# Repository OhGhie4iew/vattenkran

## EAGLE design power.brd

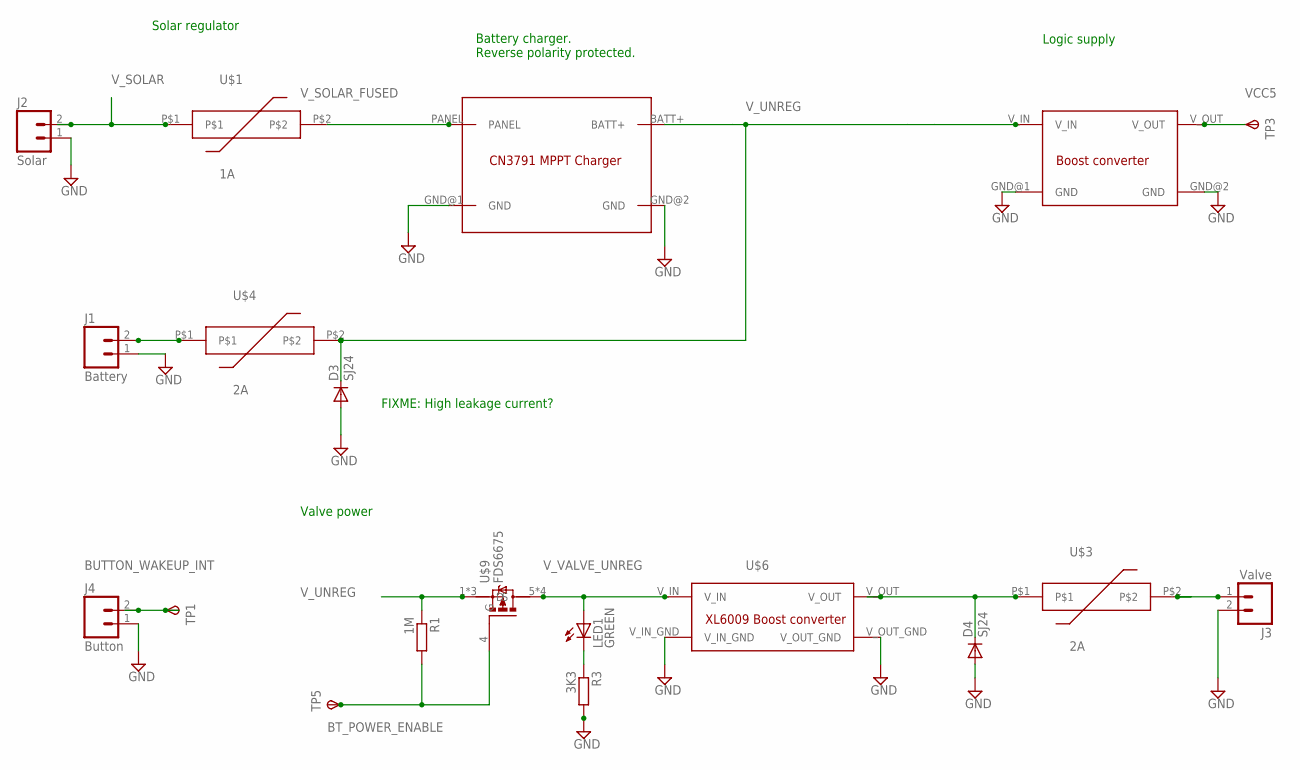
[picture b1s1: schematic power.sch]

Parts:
D3, D4: SJ24; SMB
J1: Battery; 1X02_LONGPADS
J2: Solar; 1X02_LONGPADS
J3: Valve; 1X02_LONGPADS
J4: Button; 1X02_LONGPADS
LED1: GREEN; LED3MM
R1: 1M; R0805
R3: 3K3; R0805
TP1, TP3, TP5: TPSB1,27; B1,27
U$1: 1A; 1812
U$2: CN3791_MTTP_LIPO_SOLAR_CHARGER; CN3791_MPPT_LIPO_SOLAR_CHARGER
U$3, U$4: 2A; 1812
U$5: QSKJ_BOOST_MODULE
U$6: XL6009_BOOST_MODULE
U$9: FDS6675; SO08

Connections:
BT_POWER_ENABLE: R1.2, TP5.TP, U$9.4 (G)
BUTTON_WAKEUP_INT: J4.2, TP1.TP
GND: D3.A, D4.A, J1.1, J2.1, J3.2, J4.1, R3.2, U$2.GND@1 (GND), U$2.GND@2 (GND), U$5.GND@1 (GND), U$5.GND@2 (GND), U$6.V_IN_GND, U$6.V_OUT_GND
unnamed: J1.2, U$4.P$1
unnamed: D4.C, U$3.P$1, U$6.V_OUT
unnamed: LED1.K (C), R3.1
VALVE: J3.1, U$3.P$2
VCC5: TP3.TP, U$5.V_OUT
V_SOLAR: J2.2, U$1.P$1
V_SOLAR_FUSED: U$1.P$2, U$2.PANEL
V_UNREG: D3.C, R1.1, U$2.BATT+, U$4.P$2, U$5.V_IN, U$9.1 (S), U$9.2 (S), U$9.3 (S)
V_VALVE_UNREG: LED1.A, U$6.V_IN, U$9.5 (D), U$9.6 (D), U$9.7 (D), U$9.8 (D)

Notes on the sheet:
Logic supply
Battery charger. Reverse polarity protected.
Solar regulator
FIXME: High leakage current?
Valve power

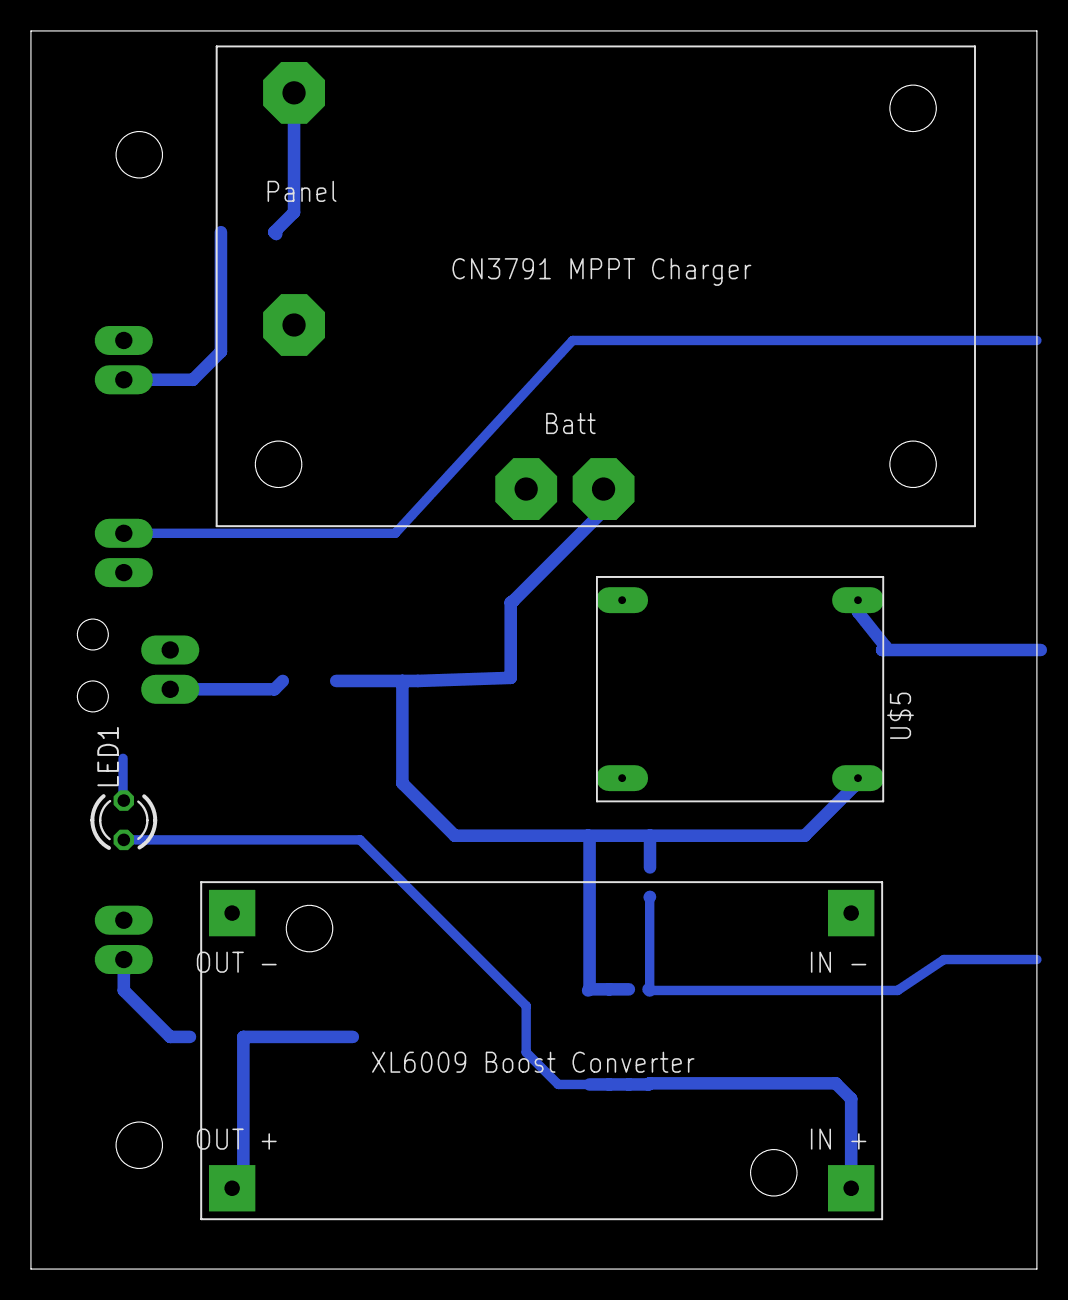
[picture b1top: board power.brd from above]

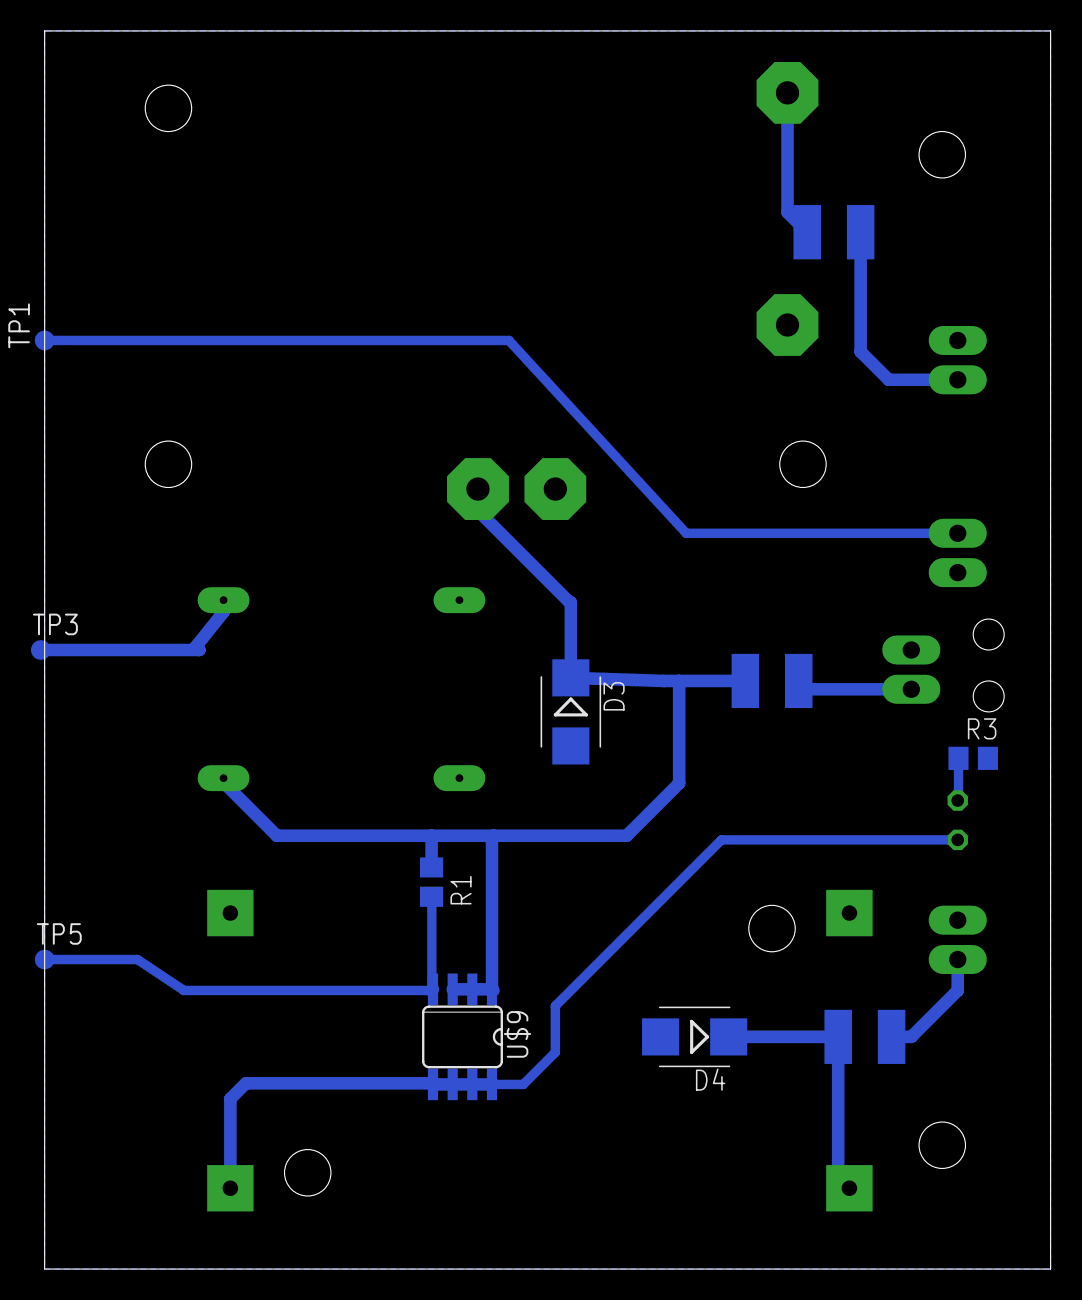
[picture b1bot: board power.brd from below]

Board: 2 copper layers, 65.0 x 80.0 mm, 19 parts (11 on the bottom side), 12 nets.

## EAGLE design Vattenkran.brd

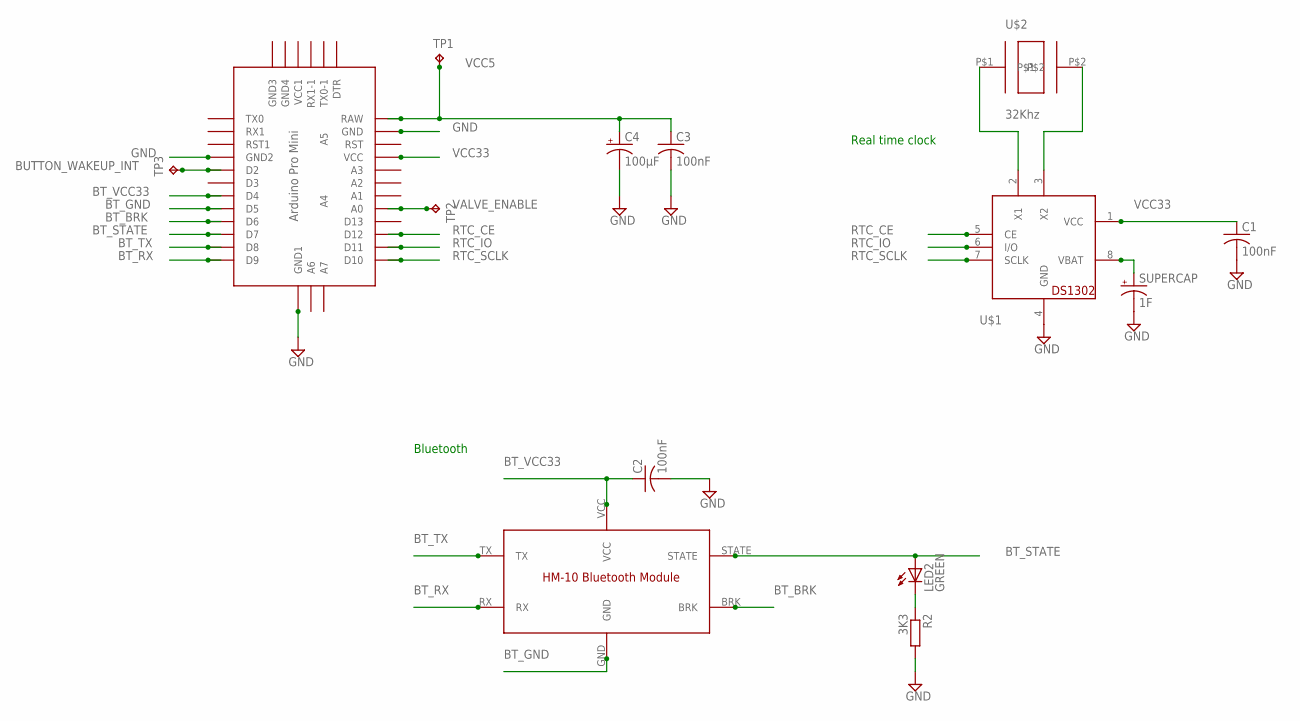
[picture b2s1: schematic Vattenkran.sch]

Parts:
C1, C2, C3: 100nF; C0805
C4: 100µF; PANASONIC_D
LED2: GREEN; LED3MM
R2: 3K3; R0805
SUPERCAP: 1F; ETR2
TP1, TP2, TP3: TPB1,27; B1,27
U$1: DS1302; SOP8
U$2: 32Khz; SM3
U$4: HM10_BLUETOOTH_MODULE
U$7: ABK-PRO-MINI

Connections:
BT_BRK: U$4.BRK, U$7.D6
BT_GND: U$4.GND, U$7.D5
BT_RX: U$4.RX, U$7.D9
BT_STATE: LED2.A, U$4.STATE, U$7.D7
BT_TX: U$4.TX, U$7.D8
BT_VCC33: C2.1, U$4.VCC, U$7.D4
BUTTON_WAKEUP_INT: TP3.TP, U$7.D2
GND: C1.2, C2.2, C3.2, C4.-, R2.2, SUPERCAP.-, U$1.4 (GND), U$7.GND, U$7.GND1 (GND2), U$7.GND4 (GND1)
unnamed: LED2.K (C), R2.1
unnamed: U$1.2 (X1), U$2.P$1
unnamed: U$1.3 (X2), U$2.P$2
RTC_CE: U$1.5 (CE), U$7.D12
RTC_IO: U$1.6 (I/O), U$7.D11
RTC_SCLK: U$1.7 (SCLK), U$7.D10
SUPERCAP: SUPERCAP.+, U$1.8 (VBAT)
VALVE_ENABLE: TP2.TP, U$7.A0
VCC5: C3.1, C4.+, TP1.TP, U$7.RAW
VCC33: C1.1, U$1.1 (VCC), U$7.VCC

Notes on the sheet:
Real time clock
Bluetooth

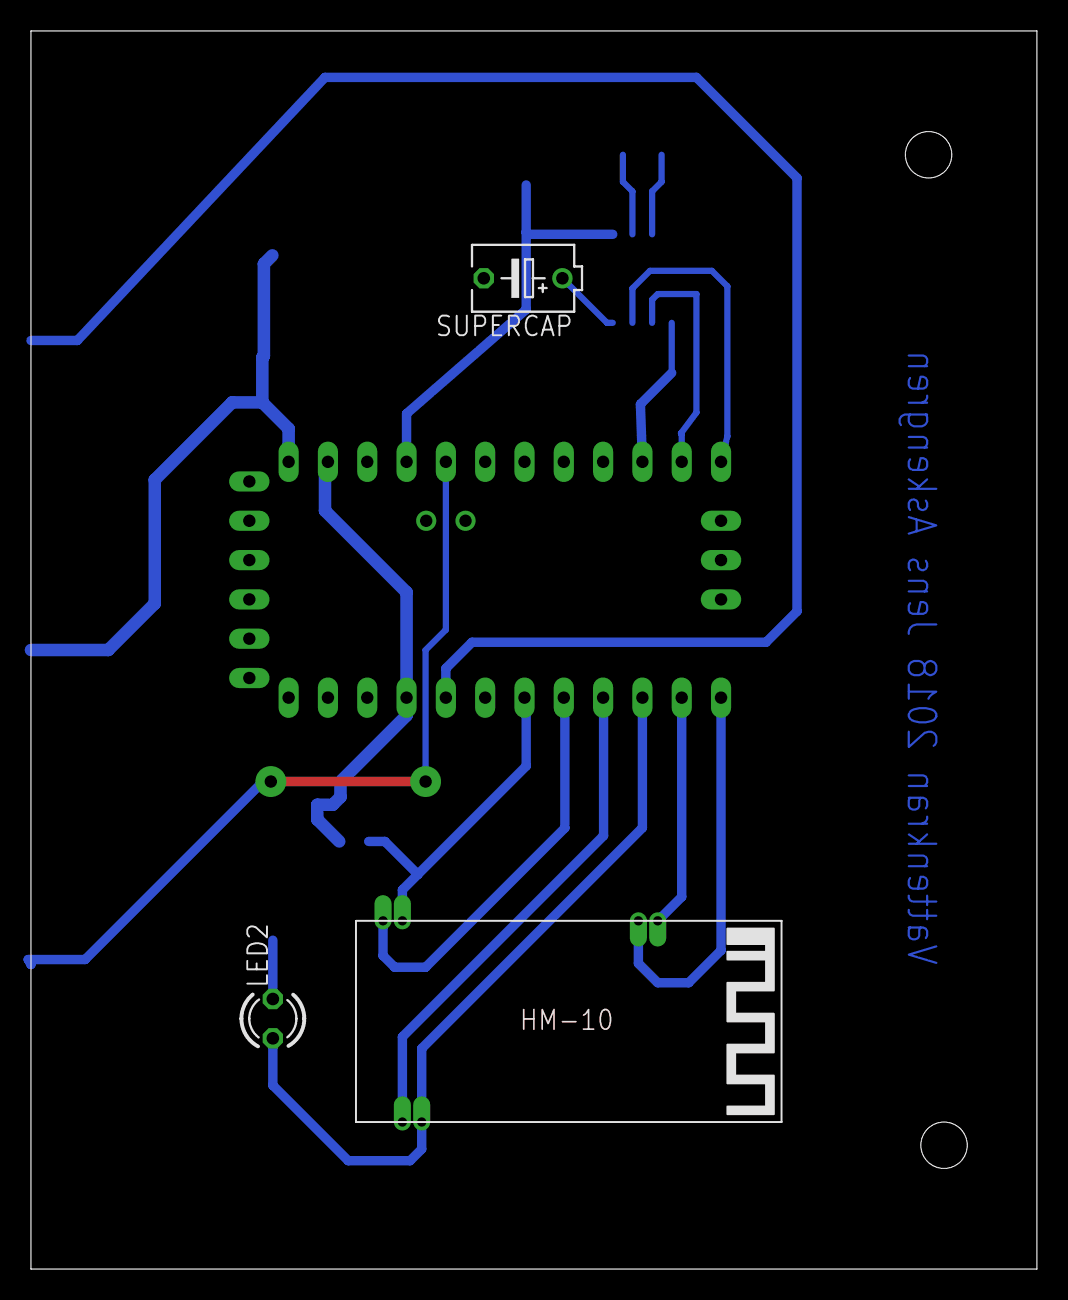
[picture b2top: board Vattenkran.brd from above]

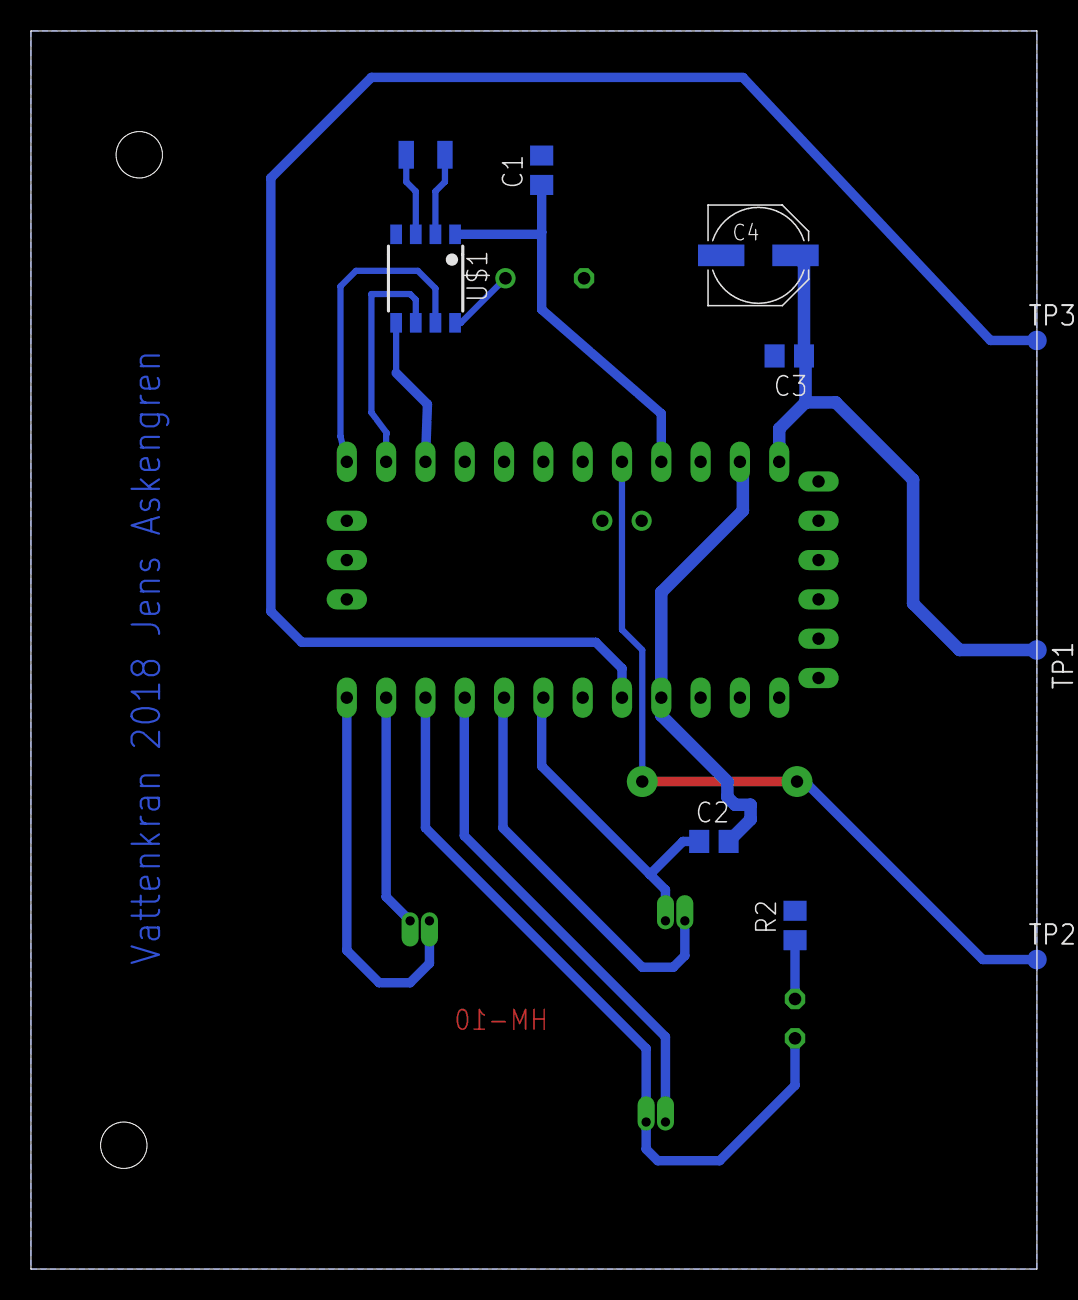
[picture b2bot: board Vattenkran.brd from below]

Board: 2 copper layers, 65.0 x 80.0 mm, 14 parts (10 on the bottom side), 18 nets.

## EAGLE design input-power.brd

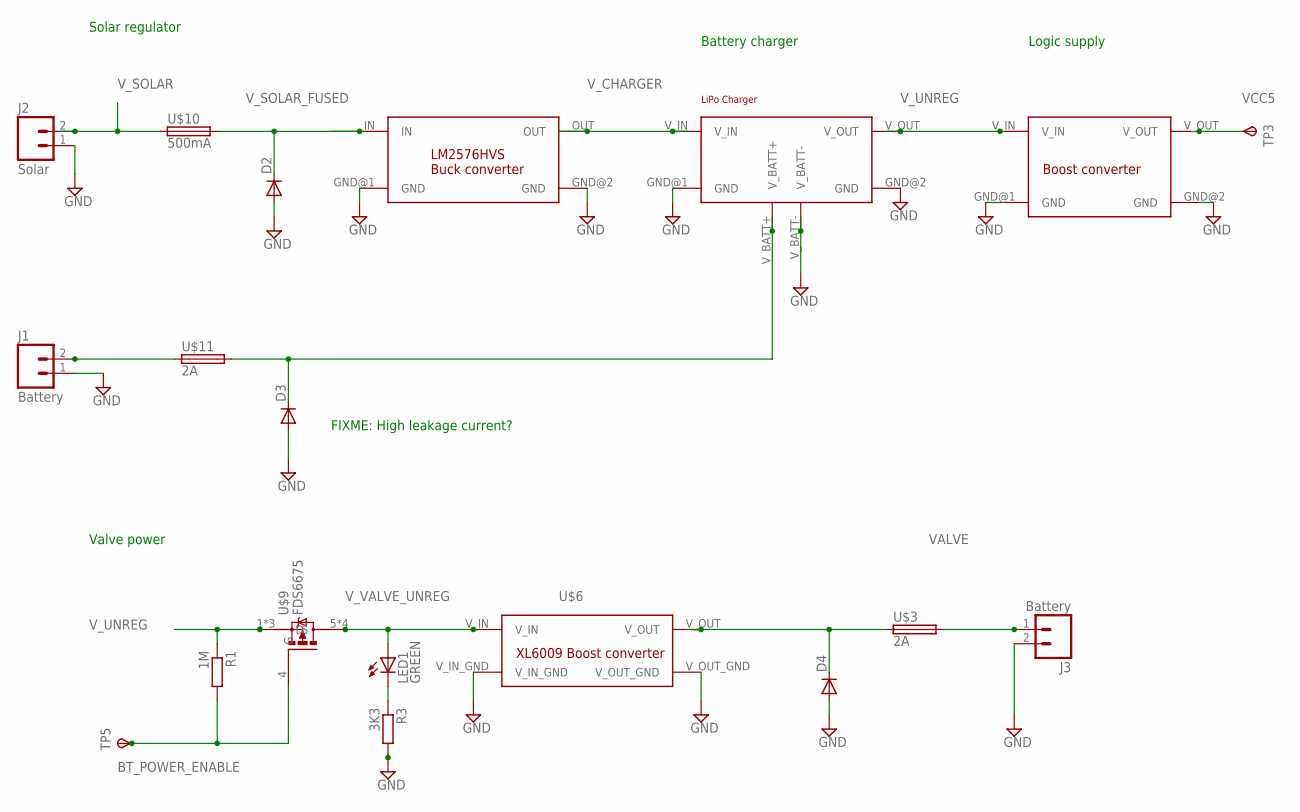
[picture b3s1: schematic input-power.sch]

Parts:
D2, D3, D4: DIODE-SMB; SMB
J1, J3: Battery; 1X02_LONGPADS
J2: Solar; 1X02_LONGPADS
LED1: GREEN; LED3MM
R1: 1M; R0805
R3: 3K3; R0805
TP3, TP5: TPSB1,27; B1,27
U$2: BATTERY_CHARGER
U$3, U$11: 2A; MF-SMDF050
U$5: QSKJ_BOOST_MODULE
U$6: XL6009_BOOST_MODULE
U$8: LM2576HVS_BUCK_MODULE
U$9: FDS6675; SO08
U$10: 500mA; MF-SMDF050

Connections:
BT_POWER_ENABLE: R1.2, TP5.TP, U$9.4 (G)
GND: D2.A, D3.A, D4.A, J1.1, J2.1, J3.2, R3.2, U$2.GND@1 (GND), U$2.GND@2 (GND), U$2.V_BATT-, U$5.GND@1 (GND), U$5.GND@2 (GND), U$6.V_IN_GND, U$6.V_OUT_GND, U$8.GND@1 (GND), U$8.GND@2 (GND)
unnamed: J1.2, U$11.1
unnamed: D4.C, U$3.1, U$6.V_OUT
unnamed: LED1.K (C), R3.1
unnamed: D3.C, U$2.V_BATT+, U$11.2
VALVE: J3.1, U$3.2
VCC5: TP3.TP, U$5.V_OUT
V_CHARGER: U$2.V_IN, U$8.OUT
V_SOLAR: J2.2, U$10.1
V_SOLAR_FUSED: D2.C, U$8.IN, U$10.2
V_UNREG: R1.1, U$2.V_OUT, U$5.V_IN, U$9.1 (S), U$9.2 (S), U$9.3 (S)
V_VALVE_UNREG: LED1.A, U$6.V_IN, U$9.5 (D), U$9.6 (D), U$9.7 (D), U$9.8 (D)

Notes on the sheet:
Logic supply
Battery charger
Solar regulator
FIXME: High leakage current?
Valve power

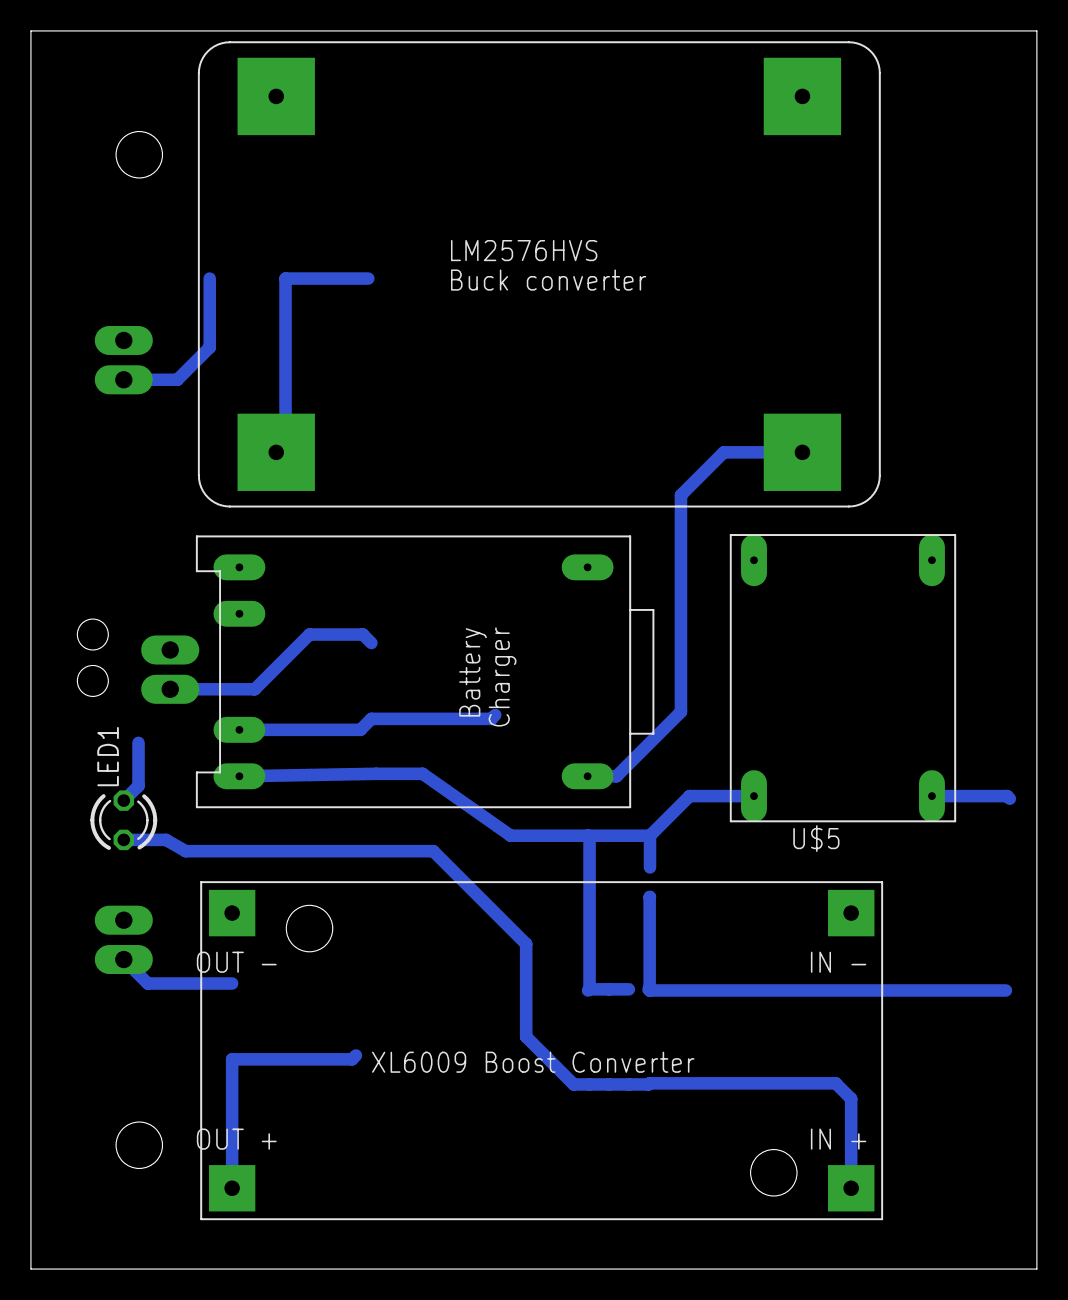
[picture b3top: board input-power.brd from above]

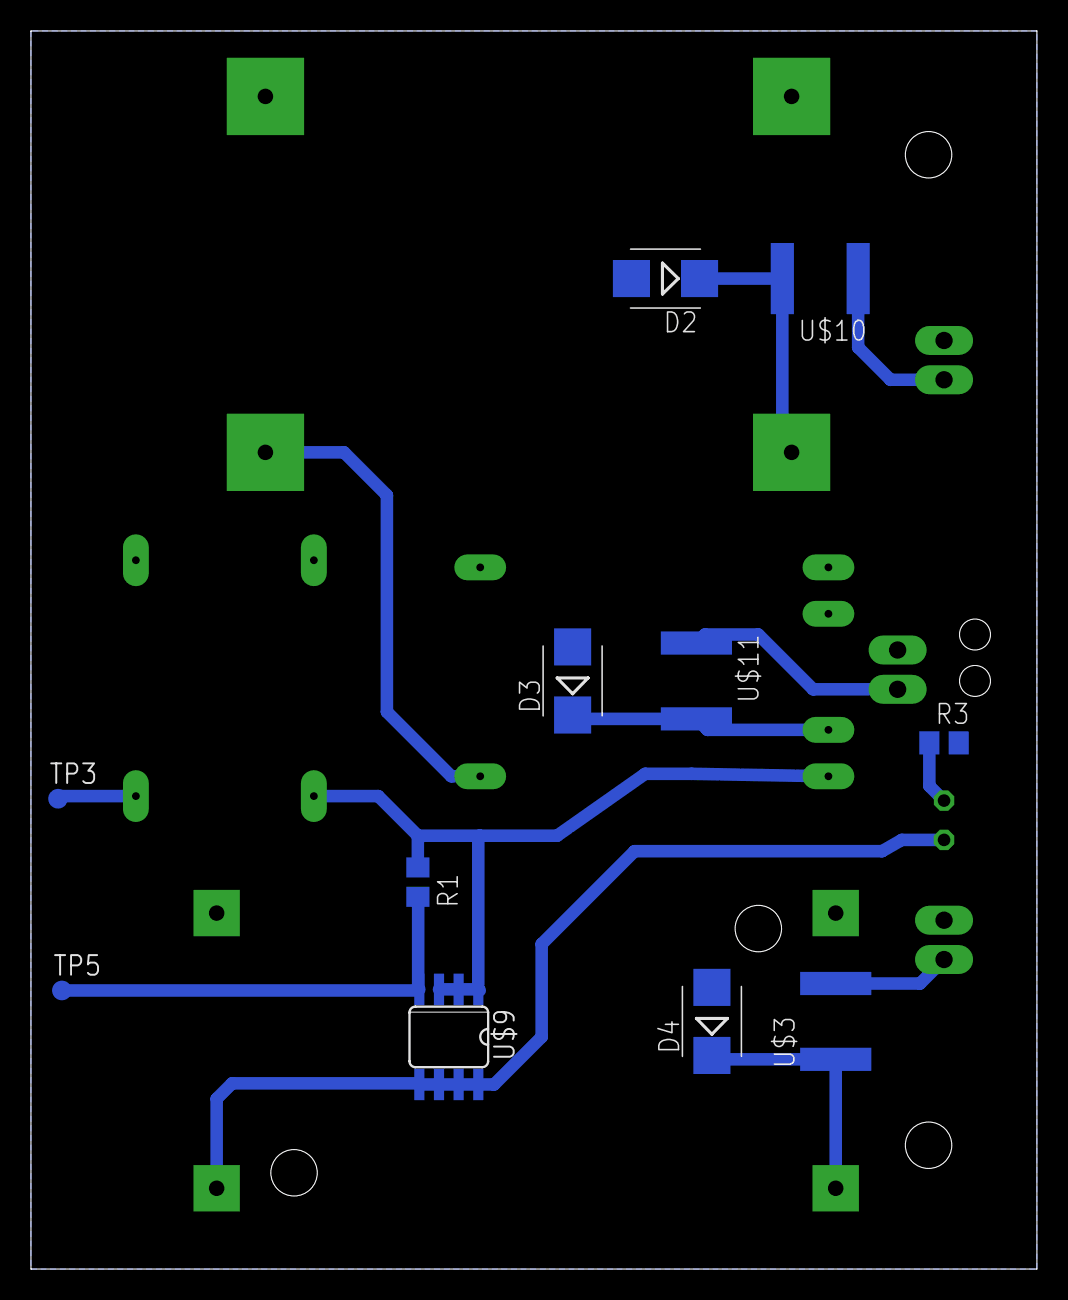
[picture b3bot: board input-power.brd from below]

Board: 2 copper layers, 65.0 x 80.0 mm, 19 parts (11 on the bottom side), 13 nets.

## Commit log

2018-10-02 Don't abort due to empty message
2018-10-02 Solar input
2018-10-03 Board
2018-10-03 Fixes
2018-10-05 Modular layout
2018-10-06 Work on power board
2018-10-07 Layout
2018-10-08 Reworked power board
2018-10-08 Fill to edge
2018-10-08 Fixed layout
2018-10-08 Replaced PTC
2018-10-08 Replaced crystal
2018-10-09 Fixed thermals size
2018-10-11 Added cap
2019-01-28 Using CN3791

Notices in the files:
parts and their libraries:
SparkFun-Connectors: Licensing: Creative Commons ShareAlike 4.0 International - https://creativecommons.org/licenses/by-sa/4.0
